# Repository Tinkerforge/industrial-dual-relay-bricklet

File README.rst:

Industrial Dual Relay Bricklet
==============================

This repository contains the firmware source code and the hardware design
files. The documentation generator configs can be found at
https://github.com/Tinkerforge/generators

Repository Content
------------------

software/:
 * examples/: Examples for all supported languages
 * build/: Compiled files
 * src/: Source code of firmware
 * Makefile: Makefile to build project

hardware/:
 * Contains KiCad project files and additionally schematics as PDF

datasheets/:
 * Contains datasheets for sensors and complex ICs that are used

Hardware
--------

The hardware is designed with the open source EDA Suite KiCad
(http://www.kicad.org). Before you are able to open the files,
you have to install the Tinkerforge kicad-libraries
(https://github.com/Tinkerforge/kicad-libraries). You can either clone
them directly in hardware/ or clone them in a separate folder and
symlink them into hardware/
(ln -s kicad_path/kicad-libraries project_path/hardware). After that you
can open the .pro file in hardware/ with KiCad and from there view and
modify the schematics and the PCB layout.

Software
--------

If you want to do your own Brick/Bricklet firmware development we highly
recommend that you use our build environment setup script and read the
tutorial (https://www.tinkerforge.com/en/doc/Tutorials/Tutorial_Build_Environment/Tutorial.html).

To compile the C code we recommend you to install the newest GNU Arm Embedded
Toolchain (https://launchpad.net/gcc-arm-embedded/+download).
You also need to install bricklib2 (https://github.com/Tinkerforge/bricklib2).

You can either clone it directly in software/src/ or clone it in a
separate folder and symlink it into software/src/
(ln -s bricklib_path/bricklib2 project_path/software/src/). Finally make sure to
have CMake installed (http://www.cmake.org/cmake/resources/software.html).

After that you can build the firmware by invoking make in software/.
The firmware (.zbin) can then be found in software/build/ and uploaded
with brickv (click button "Flashing" on start screen).

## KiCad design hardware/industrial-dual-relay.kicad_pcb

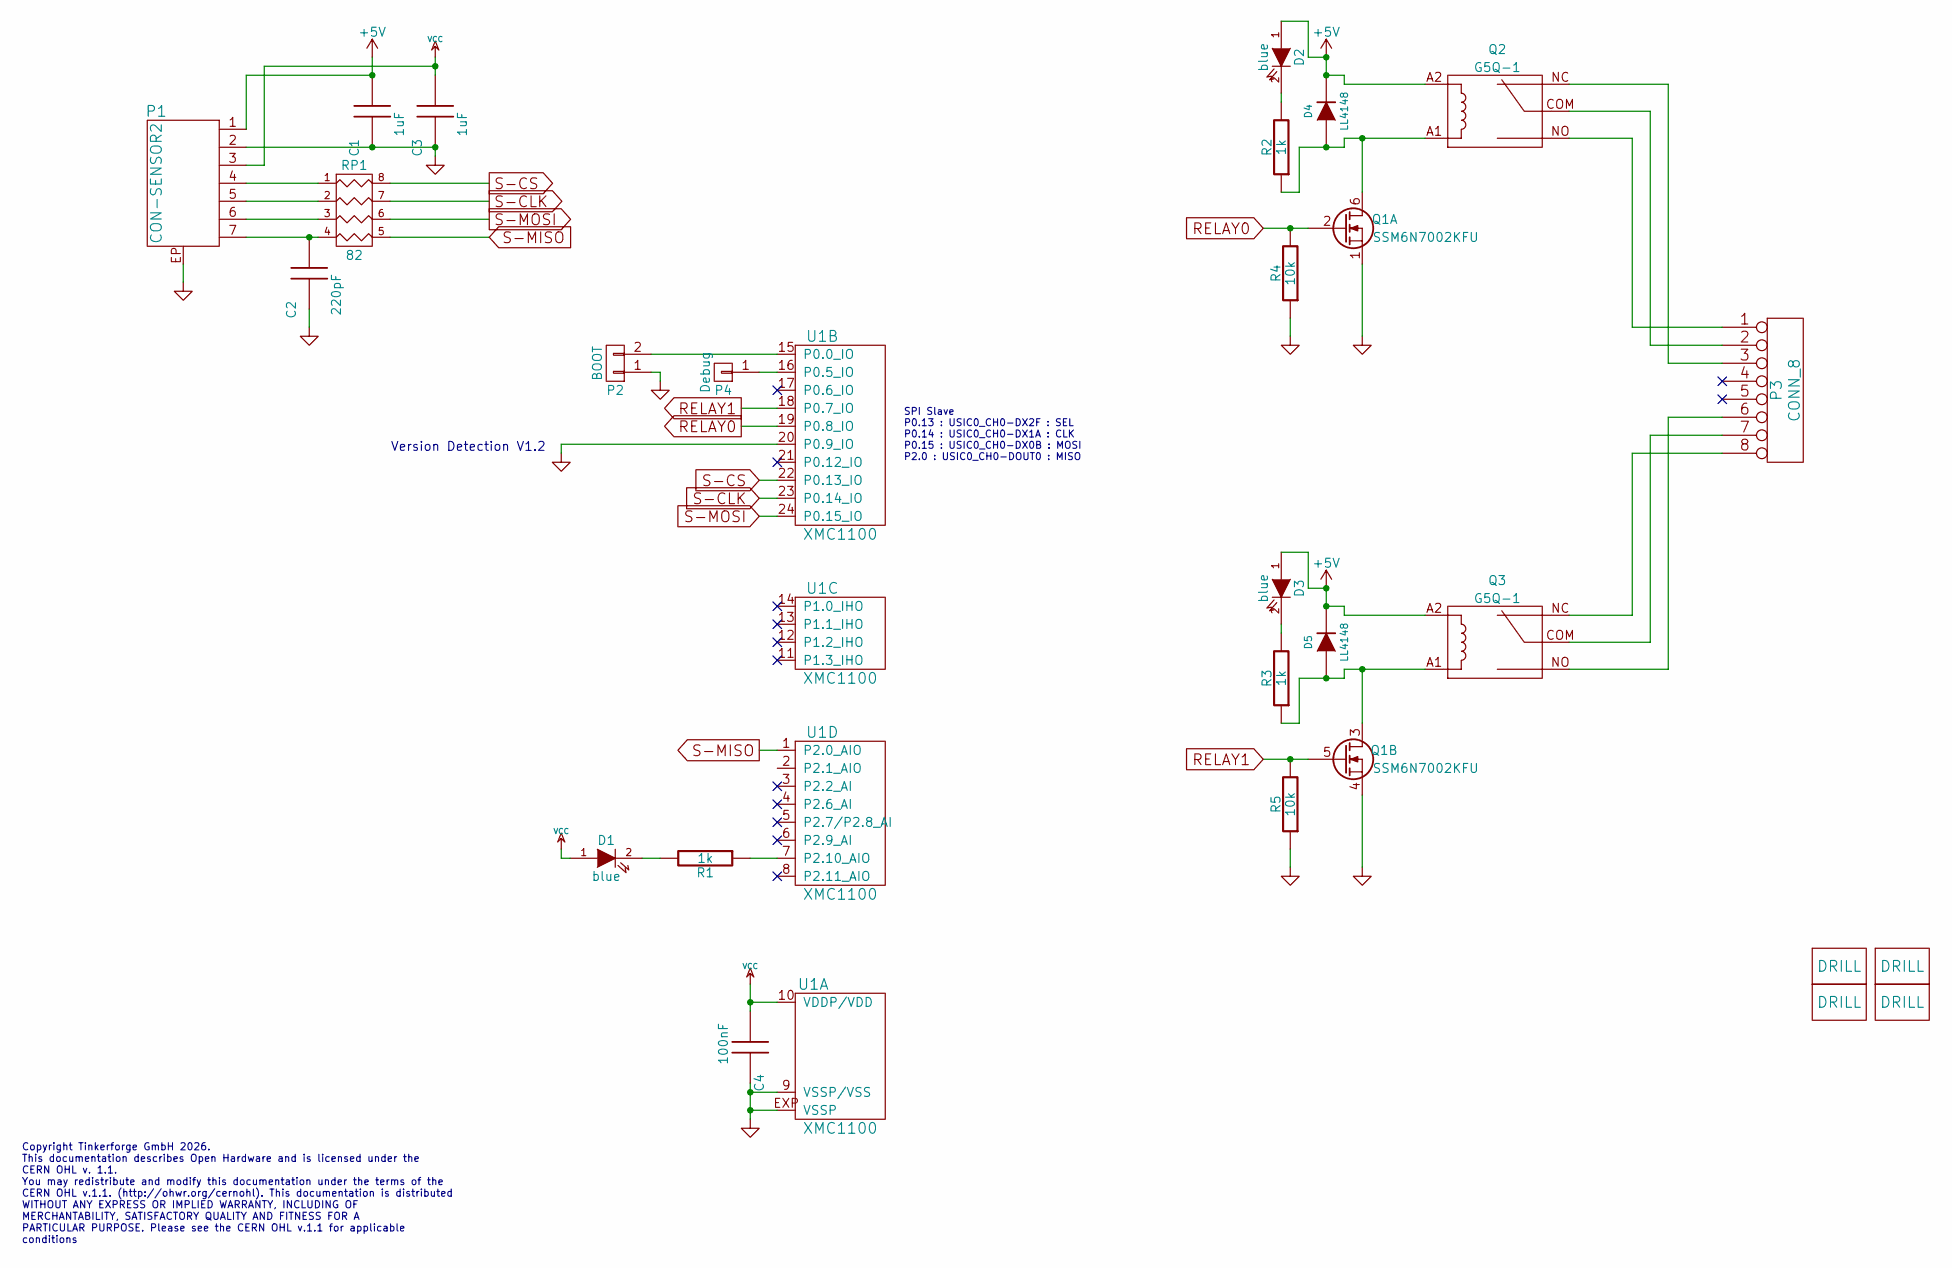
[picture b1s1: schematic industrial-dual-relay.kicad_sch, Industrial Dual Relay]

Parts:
C1, C3: 1uF; C0603F
C2: 220pF; C0402F
C4: 100nF; C0603F
D1, D2, D3: blue; D0603E
D4, D5: LL4148; MiniMelf
P1: CON-SENSOR2
P2: BOOT; SolderJumper
P3: CONN_8; OQ_8P_230V
P4: Debug; DEBUG_PAD
Q1: SSM6N7002KFU; SOT363
Q2, Q3: G5Q-1
R1, R2, R3: 1k; R0603F
R4, R5: 10k; R0402F
RP1: 82; 4X0402
U1: XMC1100; QFN24-4x4mm-0.5mm
U4, U5, U6, U7: DRILL; DRILL_NP

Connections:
+5V: C1.2, D2.1 (A), D3.1 (A), D4.2 (K), D5.2 (K), P1.1, Q2.A2, Q3.A2
GND: C1.1, C2.1, C3.1, C4.2, P1.2, P1.EP, P2.1, Q1.1 (S1), Q1.4 (S2), R4.1, R5.1, U1.9 (VSSP/VSS), U1.20 (P0.9_IO), U1.EXP (VSSP)
unnamed: D1.2 (K), R1.2
unnamed: D2.2 (K), R2.2
unnamed: D3.2 (K), R3.2
unnamed: D4.1 (A), Q1.6 (D1), Q2.A1, R2.1
unnamed: D5.1 (A), Q1.3 (D2), Q3.A1, R3.1
unnamed: P2.2, U1.15 (P0.0_IO)
unnamed: P3.1, Q2.NO
unnamed: P3.2, Q2.COM
unnamed: P3.3, Q2.NC
unnamed: P3.6, Q3.NO
unnamed: P3.7, Q3.COM
unnamed: P3.8, Q3.NC
unnamed: P4.1, U1.16 (P0.5_IO)
unnamed: P1.4, RP1.1
unnamed: P1.5, RP1.2
unnamed: P1.6, RP1.3
unnamed: C2.2, P1.7, RP1.4
unnamed: R1.1, U1.7 (P2.10_AIO)
RELAY0: Q1.2 (G1), R4.2, U1.19 (P0.8_IO)
RELAY1: Q1.5 (G2), R5.2, U1.18 (P0.7_IO)
S-CLK: RP1.7 (R2), U1.23 (P0.14_IO)
S-CS: RP1.8 (R1), U1.22 (P0.13_IO)
S-MISO: RP1.5 (R4), U1.1 (P2.0_AIO)
S-MOSI: RP1.6 (R3), U1.24 (P0.15_IO)
VCC: C3.2, C4.1, D1.1 (A), P1.3, U1.10 (VDDP/VDD)

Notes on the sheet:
Copyright Tinkerforge GmbH 2026. This documentation describes Open Hardware and is licensed under the CERN OHL v. 1.1. You may redistribute and modify this documentation under the terms of the CERN OHL v.1.1. (http://ohwr.org/cernohl). This documentation is distributed WITHOUT ANY EXPRESS OR IMPLIE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
SPI Slave P0.13 : USIC0_CH0-DX2F : SEL P0.14 : USIC0_CH0-DX1A : CLK P0.15 : USIC0_CH0-DX0B : MOSI P2.0 : USIC0_CH0-DOUT0 : MISO
Version Detection V1.2

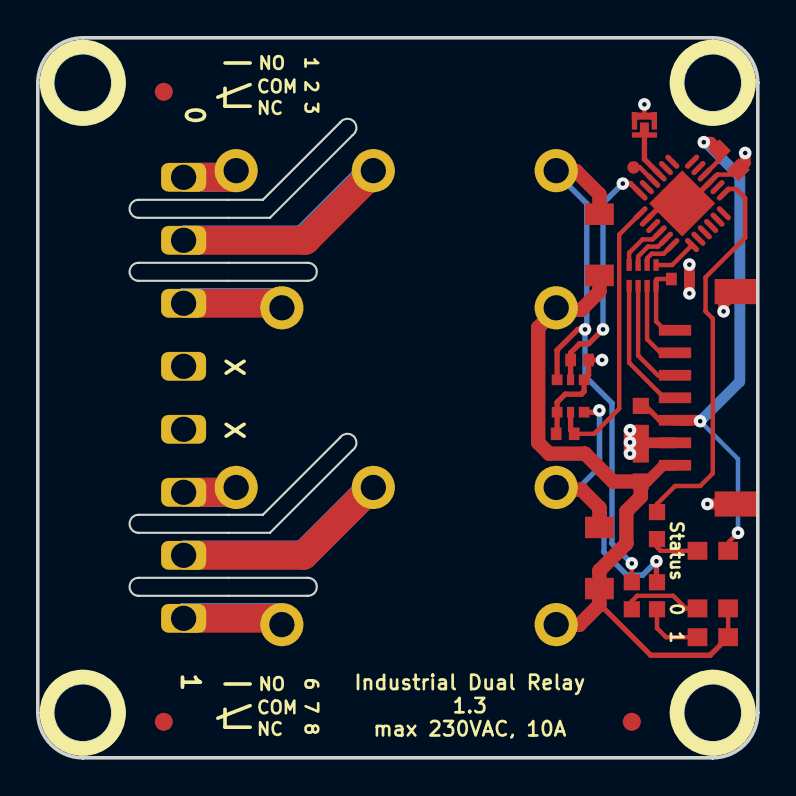
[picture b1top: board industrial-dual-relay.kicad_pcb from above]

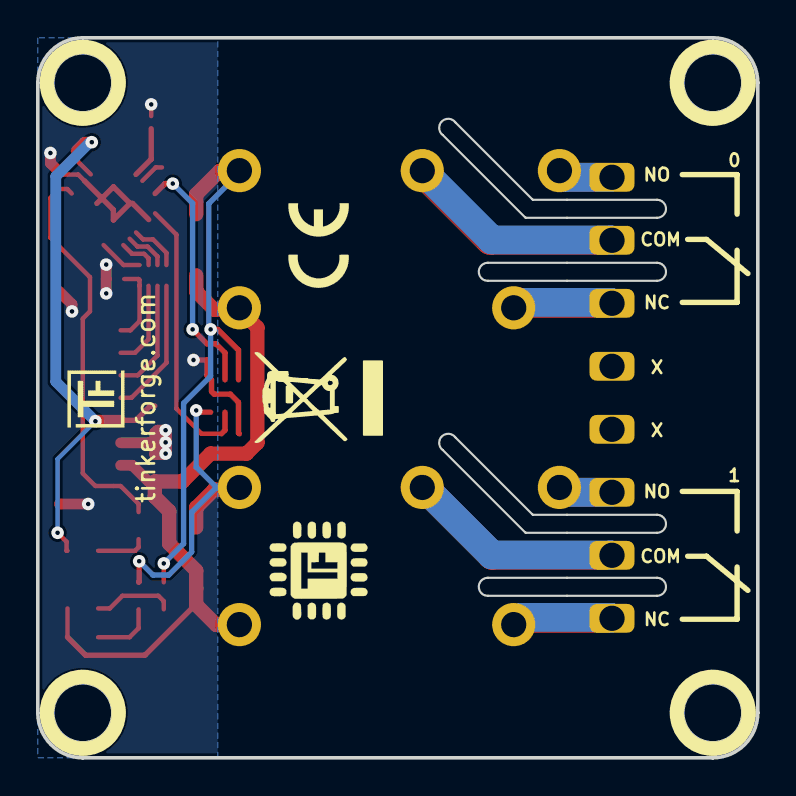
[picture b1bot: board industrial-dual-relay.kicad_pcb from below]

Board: 2 copper layers, 40.0 x 40.0 mm, 32 parts (2 on the bottom side), 27 nets.

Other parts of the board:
Fiducial_Mark: VAL**; Fiducial_Mark
Fiducial_Mark#2, Fiducial_Mark#3: VAL**; Fiducial_Mark
VAL: CE_5mm
VAL#2: WEEE_7mm

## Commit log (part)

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2017-05-29 add status leds for relays
2017-05-30 Add .gitignore
2017-05-30 Add firmware implementation
2017-05-30 Remove debug code
2017-12-06 industrial dual relay bricklet prototype finished
2017-12-06 fix description text
2017-12-07 Add examples
2018-01-22 specify values
2018-01-26 c: Fine-tune define placement
2018-02-19 javascript: Close div tag correctly
2018-02-20 Cleanup KiCad libraries config
    Ensure LibDir=kicad-libraries and LibName1=tinkerforge.
    Remove special library.
2018-03-05 Remove unused flash-size define
2018-03-08 Change name to Industrial dual Relay
2018-03-08 fix mosfet footprint
2018-03-15 fix logo positions
2018-03-16 fix tf text, add version number
2018-03-16 fix led description text
2018-03-16 Update pins to newest hardware version
2018-03-27 specify processor
2018-04-16 Add 3d information (final)
2018-04-16 Add 3d model (*.FCStd & *.wrl)
2018-05-04 Rename files
2018-05-04 Add schematic PDF
2018-05-24 perl: Use strict in examples
2018-05-24 examples: Rename Bricklet class
2018-05-25 Add LabVIEW example
2018-05-29 Rename state to value und relay1/2 to channel0/1
2018-05-29 Adapt examples to state to value rename
2018-06-07 Update changelog for initial release
2018-06-11 Fix 3d model
2018-06-18 Assign footprints to our library and remove cache library
2018-06-28 Fix readme
2018-07-11 Add Makefile with docker support
2018-07-11 Remove obsolete generate_makefile scripts
2018-07-11 Update directory structure and build instructions
2018-10-04 Increase version for new release (changes in bricklib2)
2018-10-04 Add rev to changelog
2018-11-06 Add rust examples
2018-11-07 rust: Accept host names for ip connection, fix naming inconsistencies
2018-12-14 Add go examples.
2018-12-18 go: Change import path.
2018-12-18 go: Change import path again.
2018-12-20 rust: Reformat examples.
2019-01-24 mqtt: Add examples.
2019-01-24 mqtt: Fix example header.
2019-01-24 mqtt: Remove executable bit in example permissions.
2019-01-24 go: Minor example fixes.
2019-01-24 mqtt: Minor example fixes.
2019-01-29 rust: Fix unused loop index.
2019-05-07 Don't clear monoflop time on monoflop abort to match documentation
2020-01-13 examples: Use python3 input instead of python2 raw_input.
2020-01-13 examples: mqtt: Remove trailing whitespace.
2020-03-16 Whitespace
2020-03-23 mqtt: Update for loop style
2020-04-07 examples: rust: Always block when calling bindings functions.
2020-08-19 Add uc examples.
2020-08-25 uc: Fix whitespace
2020-08-27 uc: Fix warnings.
2020-09-02 uc: Add example driver note.
2021-10-25 Update KiCad link
    https://www.kicad.org/blog/2021/10/Avoid-links-to-former-kicad-domain/
2022-04-19 examples: uc: Rename TF_HalContext to TF_HAL.
2022-04-27 uc: Adapt to bindings changes
2022-07-06 Add license files.
2022-11-15 move to kicad 6, fix schematic library links
2022-11-15 changed footprint from 8p-oq to 8p-oq-230v
2022-11-15 Version 1.1: changed relay, more clearance
2022-11-16 updated diode to minimelf footprint
2022-11-28 fiducial mark not in f.paste layer
2022-11-28 Version 1.2: Updated relay footprint
2022-11-29 Version 1.2
2023-01-04 changed relay0 and relay1 label
2023-01-24 Data cleanup.
2023-01-25 Data cleanup
2023-05-15 Add missing config_logging.h file
2025-10-04 Fix compatibility with new Docker build image (GCC 14.2.1)

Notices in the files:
hardware/industrial-dual-relay.kicad_pcb:
Licensed under CERN OHL v.1.1
Copyright (©) 2026, B.Nordmeyer
